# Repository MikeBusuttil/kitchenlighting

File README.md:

# Kitchen lighting

| 12 V minimum wiring                                                          | PCB layout                                                                                |
| ---------------------------------------------------------------------------- | ----------------------------------------------------------------------------------------- |
|  |  |

## Getting started

- install prerequisites
```sh
sudo apt install kicad kicad-symbols kicad-footprints poppler-utils python3-venv
arduino-cli core install arduino:samd
```

- build artifacts
```sh
python3 12v/build.py
python3 5v/build.py
python3 12v/pcb/pcb.py

mkdir -p 12vRGB
cp 12v/min.ino 12vRGB/12vRGB.ino
arduino-cli compile --fqbn arduino:samd:nano_33_iot --output-dir 12vRGB/build 12vRGB
```

- upload sketch to the nano
```sh
arduino-cli board list
nano_port=/dev/ttyACM0  # Replace with your Nano's port from the list above.
arduino-cli upload --fqbn arduino:samd:nano_33_iot  --port "$nano_port" --input-dir 12vRGB/build 12vRGB
```

## Project files

| Design     | Spec                   | Shopping lists                                    | Best practice       | Minimum            |
| ---------- | ---------------------- | ------------------------------------------------- | ------------------- | ------------------ |
| 12 V RGB   | [spec.md](12v/spec.md) | [min.csv](12v/min.csv) · [best.csv](12v/best.csv) | [SVG](12v/best.svg) | [SVG](12v/min.svg) |
| 5 V APA102 | [spec.md](5v/spec.md)  | [min.csv](5v/min.csv) · [best.csv](5v/best.csv)   | [SVG](5v/best.svg)  | [SVG](5v/min.svg)  |

The generated `min.csv` and `best.csv` shopping lists are compatible with DigiKey’s [Upload a List](https://www.digikey.ca/en/mylists/) feature.

## 12 V PCB

| Drawing                                          | PDF                                 |
| ------------------------------------------------ | ----------------------------------- |
| Schematic                                        | [PDF](12v/pcb/pcb.pdf)              |
| Assembly layout, dimensions and component legend | [PDF](12v/pcb/pcb-layout.pdf)       |
| Plated drill map                                 | [PDF](12v/pcb/pcb-PTH-drl_map.pdf)  |
| Non-plated drill map                             | [PDF](12v/pcb/pcb-NPTH-drl_map.pdf) |

| File                                                 | Purpose                             |
| ---------------------------------------------------- | ----------------------------------- |
| [pcb-notes.md](12v/pcb/pcb-notes.md)                 | Design, ordering, wiring and checks |
| [pcb-cost-estimate.md](12v/pcb/pcb-cost-estimate.md) | Prototype budget in CAD             |
| [pcb.kicad_pro](12v/pcb/pcb.kicad_pro)               | Editable KiCad project              |
| [pcb-gerbers.zip](12v/pcb/pcb-gerbers.zip)           | PCB fabrication upload              |
| [pcb-assembly.zip](12v/pcb/pcb-assembly.zip)         | Complete assembly handoff           |
| [pcb-bom.csv](12v/pcb/pcb-bom.csv)                   | Fitted parts                        |
| [pcb-positions.csv](12v/pcb/pcb-positions.csv)       | Placement data                      |
| [pcb-checks.json](12v/pcb/pcb-checks.json)           | Generated verification results      |

```bash
python3 12v/pcb/pcb.py            # check and export the committed CAD
python3 12v/pcb/pcb.py --rebuild  # reconstruct CAD from the circuit and saved routing
python3 -m unittest discover -s 12v/pcb -p 'test_*.py'
python3 12v/pcb/browser_exports.py  # refresh browser versions of all repository PDFs
```

## Tests

```sh
python3 -m unittest discover -s .utils -p 'test_*.py'
g++ -std=c++11 -Wall -Wextra -Werror -I12v/tests 12v/tests/test_min.cpp -o /tmp/kitchenlighting-test-min
/tmp/kitchenlighting-test-min
```

## Contributing

- markdown tables: `|`s should line up
- diagram preferences:
  - show part numbers; avoid reference codes
  - maximize readability:
    - shorter wires is better
  - avoid using a legend:
    - label components directly
    - draw all connections
  - avoid redundancy (ie. explaining a connection that the diagram clearly displays)

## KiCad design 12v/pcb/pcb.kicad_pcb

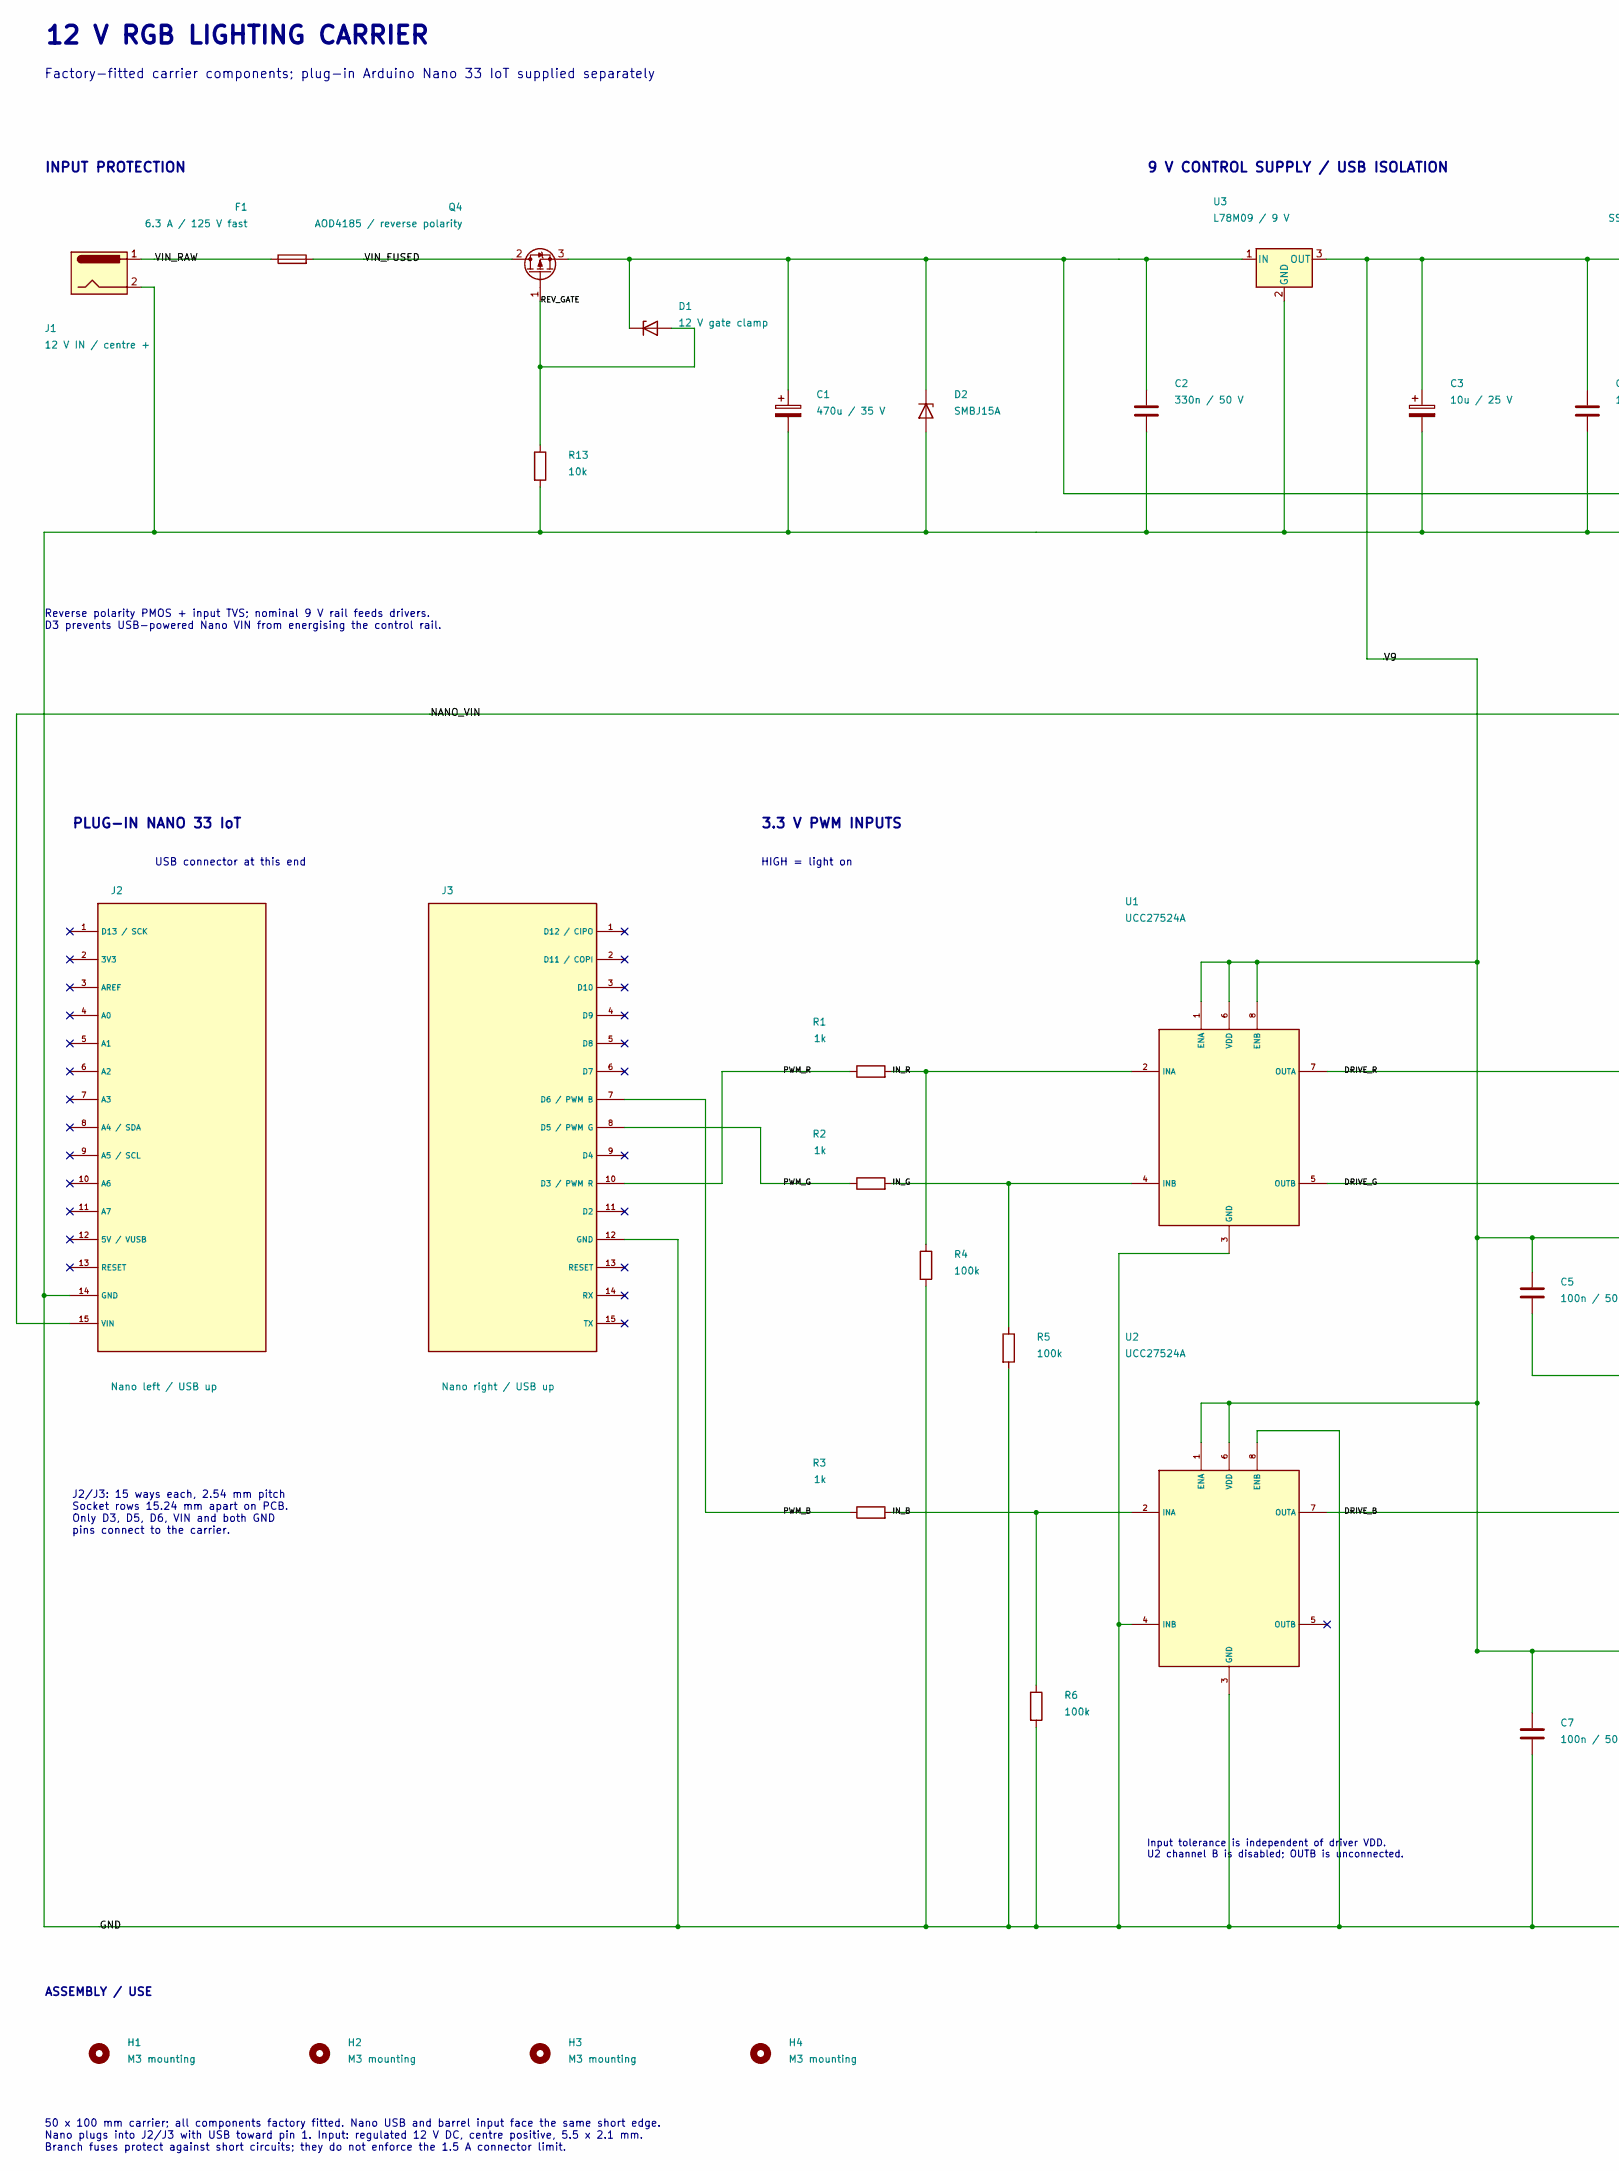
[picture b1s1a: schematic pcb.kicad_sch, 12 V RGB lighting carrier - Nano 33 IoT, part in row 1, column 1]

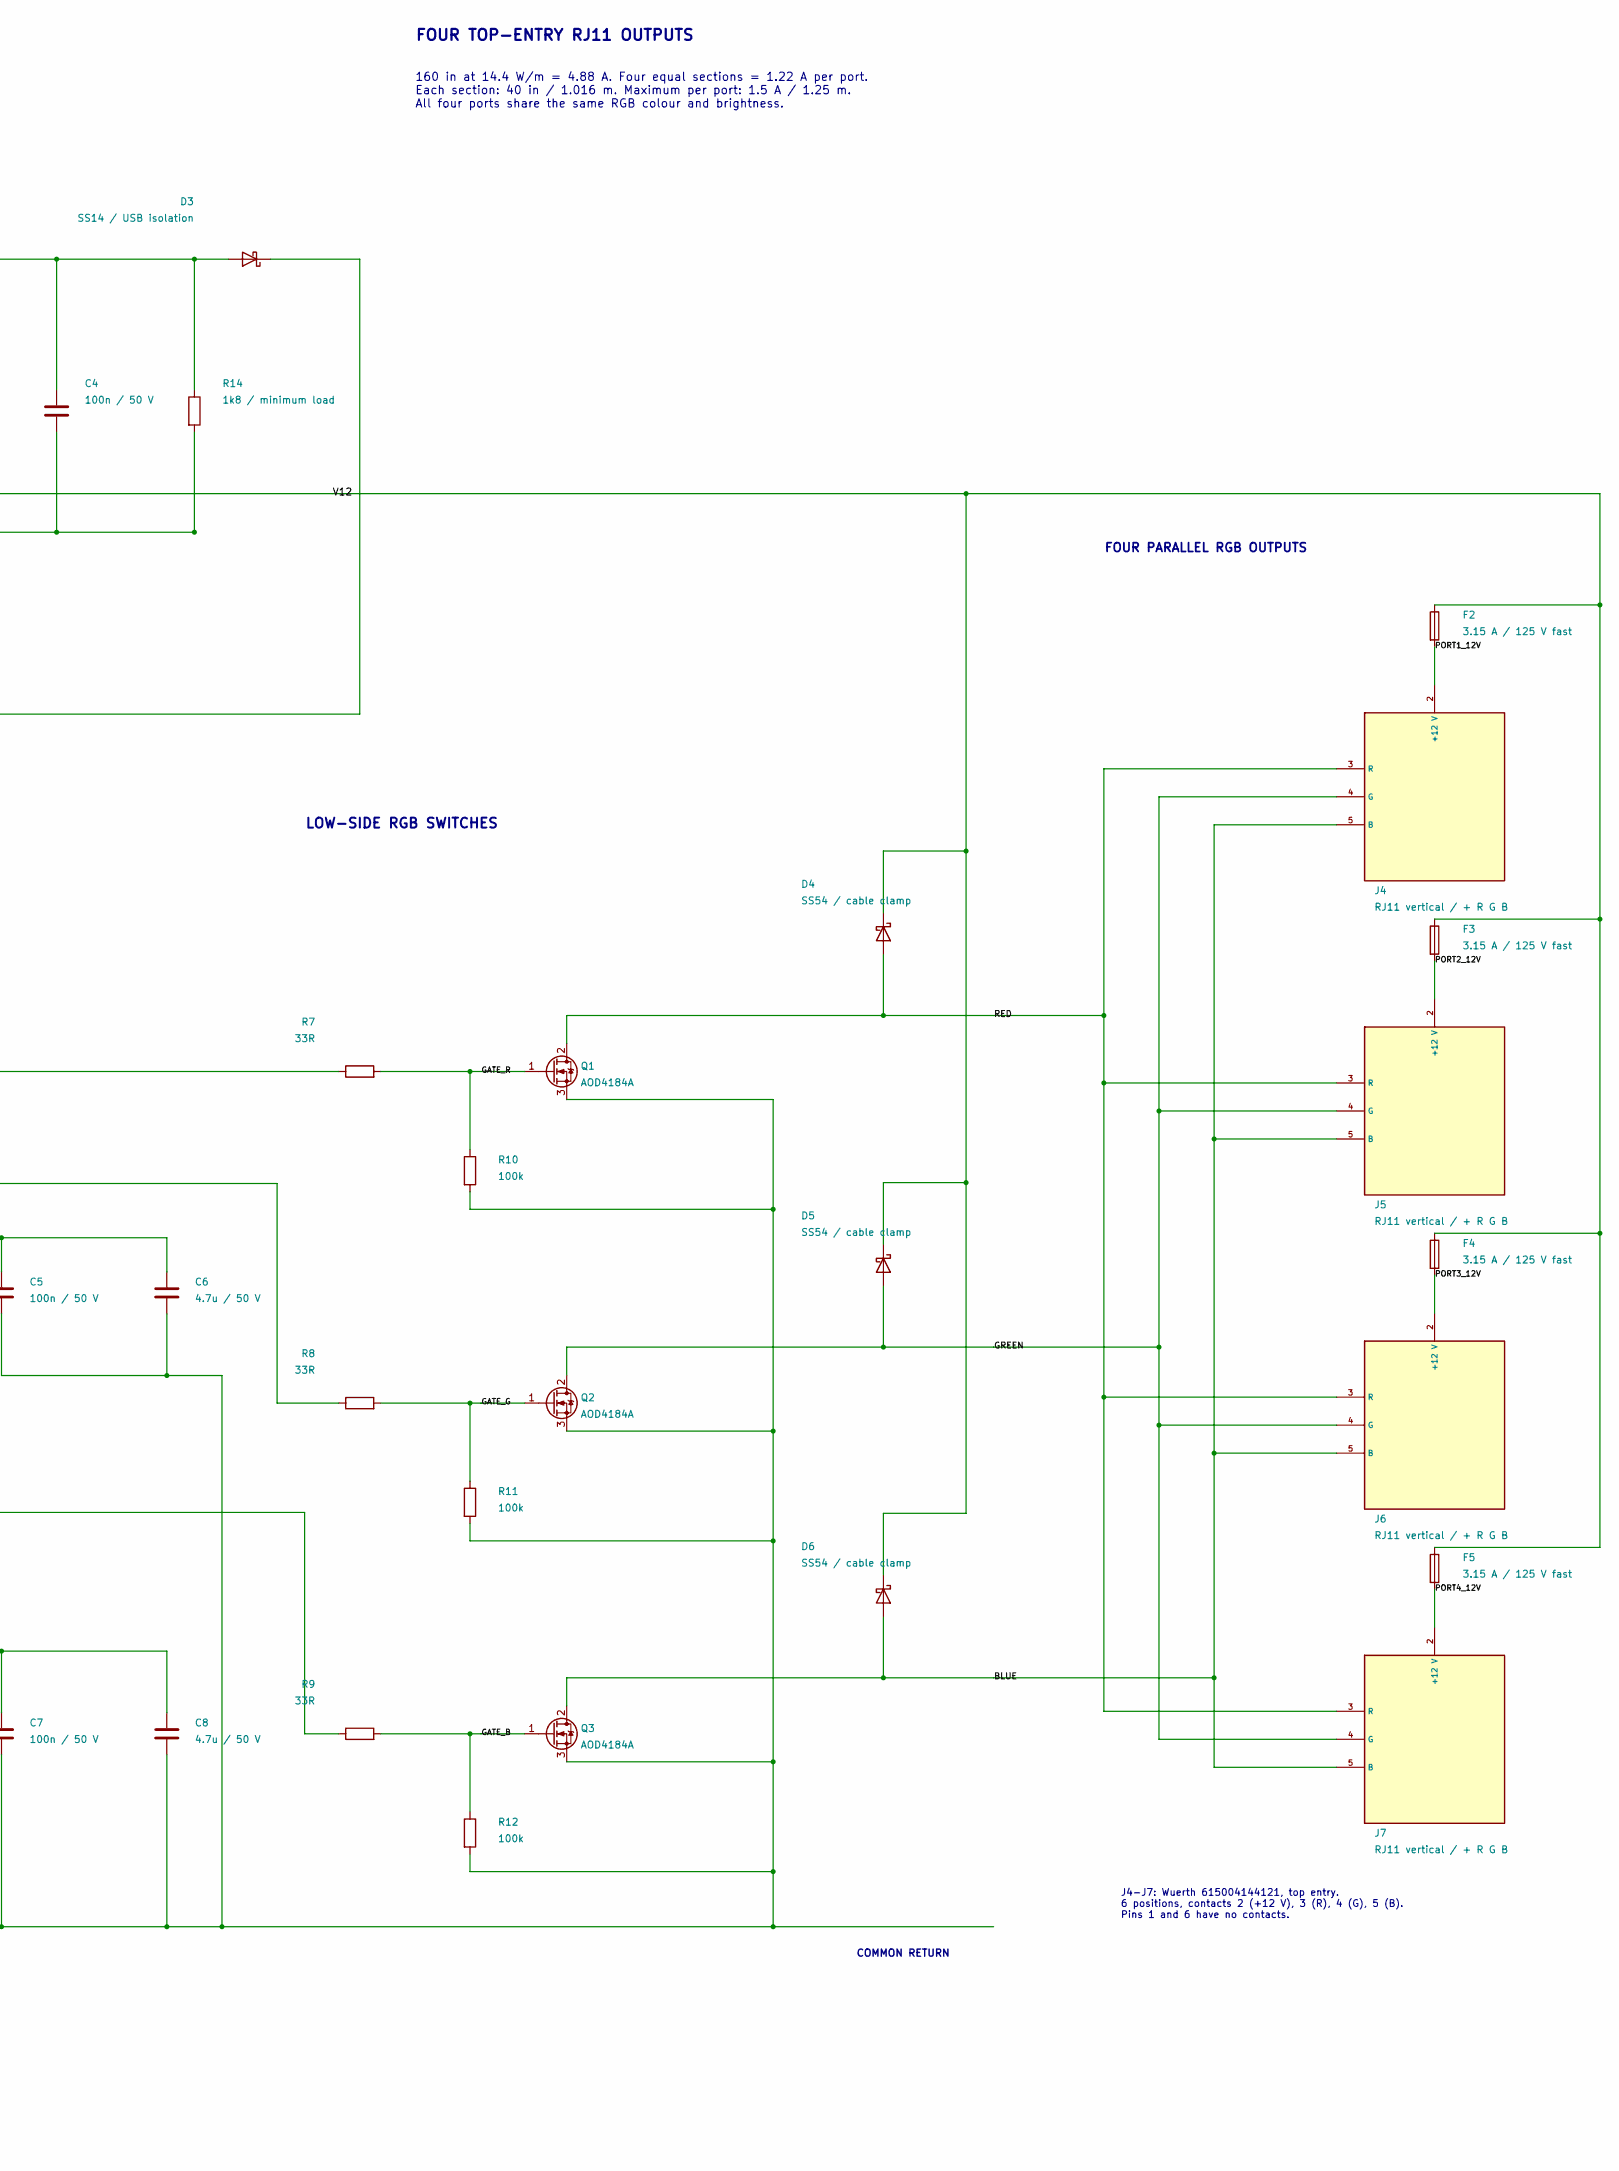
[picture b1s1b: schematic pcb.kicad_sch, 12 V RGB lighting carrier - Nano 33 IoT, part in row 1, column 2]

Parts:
C1: 470u / 35 V; CP_Elec_10x10.5; MPN EEHZL1V471P
C2: 330n / 50 V; C_0805_2012Metric; MPN GRM21BR71H334KA01L
C3: 10u / 25 V; CP_Elec_4x5.8; MPN EEEFK1E100R
C4, C5, C7: 100n / 50 V; C_0805_2012Metric; MPN GRM21BR71H104KA01L
C6, C8: 4.7u / 50 V; C_1210_3225Metric; MPN GRM32ER71H475KA88L
D1: 12 V gate clamp; D_SOD-123; MPN BZT52C12-7-F
D2: SMBJ15A; D_SMB; MPN SMBJ15A
D3: SS14 / USB isolation; D_SMA; MPN SS14-E3/61T
D4, D5, D6: SS54 / cable clamp; D_SMC; MPN SSC54-E3/57T
F1: 6.3 A / 125 V fast; Fuse_Littelfuse-NANO2-451_453; MPN 045106.3MRL
F2, F3, F4, F5: 3.15 A / 125 V fast; Fuse_Littelfuse-NANO2-451_453; MPN 04513.15MRL
H1, H2, H3, H4: M3 mounting; MountingHole_3.2mm_M3
J1: 12 V IN / centre +; BarrelJack_CUI_PJ-063AH_Horizontal; MPN PJ-063AH
J2: Nano left / USB up; Socket_Samtec_SSQ-115-01-G-S; MPN SSQ-115-01-G-S
J3: Nano right / USB up; Socket_Samtec_SSQ-115-01-G-S; MPN SSQ-115-01-G-S
J4, J5, J6, J7: RJ11 vertical / + R G B; RJ11_Wuerth_615004144121; MPN 615004144121
Q1, Q2, Q3: AOD4184A; TO-252-3_TabPin2; MPN AOD4184A
Q4: AOD4185 / reverse polarity; TO-252-3_TabPin2; MPN AOD4185
R1, R2, R3: 1k; R_0805_2012Metric; MPN RC0805FR-071KL
R4, R5, R6, R10, R11, R12: 100k; R_0805_2012Metric; MPN RC0805FR-07100KL
R7, R8, R9: 33R; R_0805_2012Metric; MPN RC0805FR-0733RL
R13: 10k; R_0805_2012Metric; MPN RC0805FR-0710KL
R14: 1k8 / minimum load; R_0805_2012Metric; MPN RC0805FR-071K8L
U1, U2: UCC27524A; SOIC-8_3.9x4.9mm_P1.27mm; MPN UCC27524ADR
U3: L78M09 / 9 V; TO-252-3_TabPin2; MPN L78M09CDT-TR

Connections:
BLUE: D6.2 (A), J4.5 (B), J5.5 (B), J6.5 (B), J7.5 (B), Q3.2 (D)
DRIVE_B: R9.1, U2.7 (OUTA)
DRIVE_G: R8.1, U1.5 (OUTB)
DRIVE_R: R7.1, U1.7 (OUTA)
GATE_B: Q3.1 (G), R9.2, R12.1
GATE_G: Q2.1 (G), R8.2, R11.1
GATE_R: Q1.1 (G), R7.2, R10.1
GND: C1.2, C2.2, C3.2, C4.2, C5.2, C6.2, C7.2, C8.2, D2.2 (A), J1.2, J2.14 (GND), J3.12 (GND), Q1.3 (S), Q2.3 (S), Q3.3 (S), R4.2, R5.2, R6.2, R10.2, R11.2, R12.2, R13.2, R14.2, U1.3 (GND), U2.3 (GND), U2.4 (INB), U2.8 (ENB), U3.2 (GND)
GREEN: D5.2 (A), J4.4 (G), J5.4 (G), J6.4 (G), J7.4 (G), Q2.2 (D)
IN_B: R3.2, R6.1, U2.2 (INA)
IN_G: R2.2, R5.1, U1.4 (INB)
IN_R: R1.2, R4.1, U1.2 (INA)
NANO_VIN: D3.1 (K), J2.15 (VIN)
PORT1_12V: F2.2, J4.2 (+12 V)
PORT2_12V: F3.2, J5.2 (+12 V)
PORT3_12V: F4.2, J6.2 (+12 V)
PORT4_12V: F5.2, J7.2 (+12 V)
PWM_B: J3.7 (D6 / PWM B), R3.1
PWM_G: J3.8 (D5 / PWM G), R2.1
PWM_R: J3.10 (D3 / PWM R), R1.1
RED: D4.2 (A), J4.3 (R), J5.3 (R), J6.3 (R), J7.3 (R), Q1.2 (D)
REV_GATE: D1.2 (A), Q4.1 (G), R13.1
V9: C3.1, C4.1, C5.1, C6.1, C7.1, C8.1, D3.2 (A), R14.1, U1.1 (ENA), U1.6 (VDD), U1.8 (ENB), U2.1 (ENA), U2.6 (VDD), U3.3 (OUT)
V12: C1.1, C2.1, D1.1 (K), D2.1 (K), D4.1 (K), D5.1 (K), D6.1 (K), F2.1, F3.1, F4.1, F5.1, Q4.3 (S), U3.1 (IN)
VIN_FUSED: F1.2, Q4.2 (D)
VIN_RAW: F1.1, J1.1

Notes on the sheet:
12 V RGB LIGHTING CARRIER
Factory-fitted carrier components; plug-in Arduino Nano 33 IoT supplied separately
FOUR TOP-ENTRY RJ11 OUTPUTS
160 in at 14.4 W/m = 4.88 A. Four equal sections = 1.22 A per port. Each section: 40 in / 1.016 m. Maximum per port: 1.5 A / 1.25 m. All four ports share the same RGB colour and brightness.
COMMON RETURN
INPUT PROTECTION
9 V CONTROL SUPPLY / USB ISOLATION
Reverse polarity PMOS + input TVS; nominal 9 V rail feeds drivers. D3 prevents USB-powered Nano VIN from energising the control rail.
PLUG-IN NANO 33 IoT
USB connector at this end
J2/J3: 15 ways each, 2.54 mm pitch Socket rows 15.24 mm apart on PCB. Only D3, D5, D6, VIN and both GND pins connect to the carrier.
3.3 V PWM INPUTS
HIGH = light on
Input tolerance is independent of driver VDD. U2 channel B is disabled; OUTB is unconnected.
LOW-SIDE RGB SWITCHES
FOUR PARALLEL RGB OUTPUTS
J4-J7: Wuerth 615004144121, top entry. 6 positions, contacts 2 (+12 V), 3 (R), 4 (G), 5 (B). Pins 1 and 6 have no contacts.
ASSEMBLY / USE
50 x 100 mm carrier; all components factory fitted. Nano USB and barrel input face the same short edge. Nano plugs into J2/J3 with USB toward pin 1. Input: regulated 12 V DC, centre positive, 5.5 x 2.1 mm. Branch fuses protect against short circuits; they do not enforce the 1.5 A connector limit.

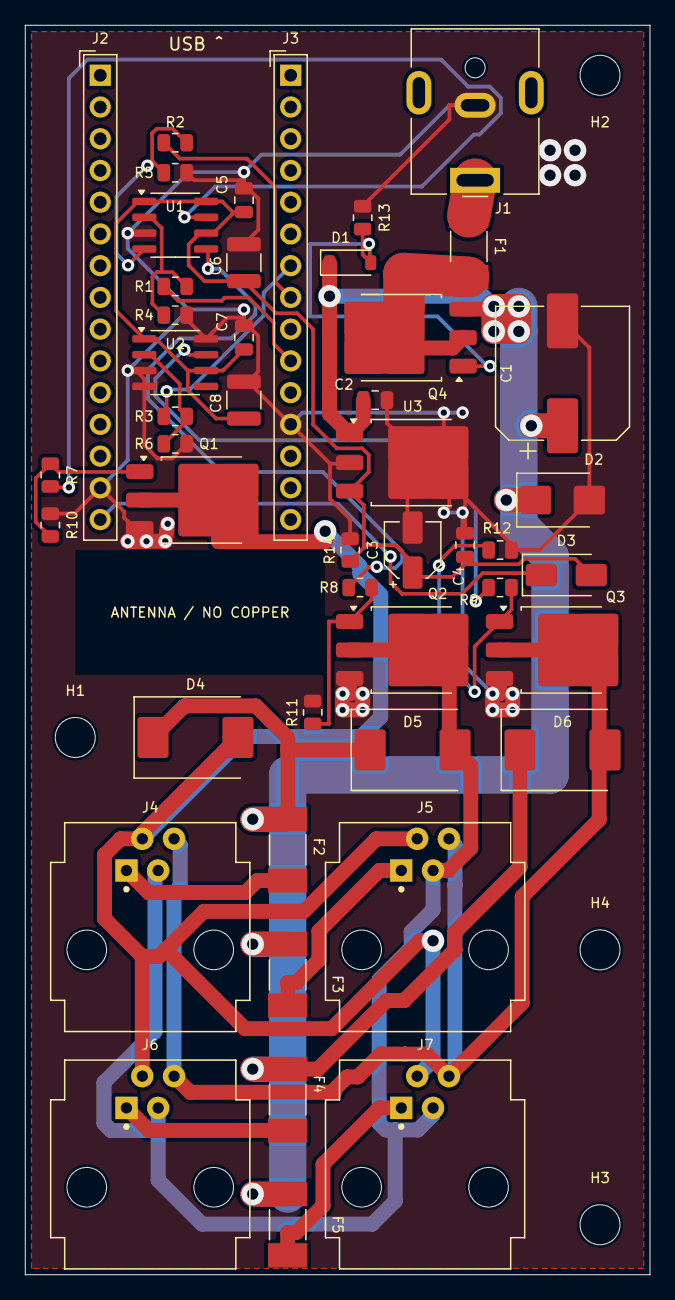
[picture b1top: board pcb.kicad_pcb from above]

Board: 2 copper layers, 50.0 x 100.0 mm, 51 parts (0 on the bottom side), 26 nets.

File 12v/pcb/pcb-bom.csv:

Designator,Quantity,Value,Manufacturer Part Number,Footprint,Assembly,Notes
J1,1,12 V IN / centre +,PJ-063AH,Connector_BarrelJack:BarrelJack_CUI_PJ-063AH_Horizontal,THT factory solder,8 A jack; 5.5 x 2.1 mm mating plug; plated slots required
J2,1,Nano left / USB up,SSQ-115-01-G-S,pcb:Socket_Samtec_SSQ-115-01-G-S,THT factory solder,2.54 mm pitch; two rows 15.24 mm apart; socket body height 8.51 mm
J3,1,Nano right / USB up,SSQ-115-01-G-S,pcb:Socket_Samtec_SSQ-115-01-G-S,THT factory solder,2.54 mm pitch; two rows 15.24 mm apart; socket body height 8.51 mm
"J4,J5,J6,J7",4,RJ11 vertical / + R G B,615004144121,pcb:RJ11_Wuerth_615004144121,THT factory solder,"Top-entry 6P4C; 1.5 A/contact; 1.25 m maximum strip at 14.4 W/m, 12 V"
F1,1,6.3 A / 125 V fast,045106.3MRL,Fuse:Fuse_Littelfuse-NANO2-451_453,Top SMT,
Q4,1,AOD4185 / reverse polarity,AOD4185,Package_TO_SOT_SMD:TO-252-3_TabPin2,Top SMT,
R13,1,10k,RC0805FR-0710KL,Resistor_SMD:R_0805_2012Metric,Top SMT,
D1,1,12 V gate clamp,BZT52C12-7-F,Diode_SMD:D_SOD-123,Top SMT,
D2,1,SMBJ15A,SMBJ15A,Diode_SMD:D_SMB,Top SMT,
C1,1,470u / 35 V,EEHZL1V471P,Capacitor_SMD:CP_Elec_10x10.5,Top SMT,
"F2,F3,F4,F5",4,3.15 A / 125 V fast,04513.15MRL,Fuse:Fuse_Littelfuse-NANO2-451_453,Top SMT,Short-circuit fuse; does NOT protect the 1.5 A RJ11 contact from overload
U3,1,L78M09 / 9 V,L78M09CDT-TR,Package_TO_SOT_SMD:TO-252-3_TabPin2,Top SMT,
C2,1,330n / 50 V,GRM21BR71H334KA01L,Capacitor_SMD:C_0805_2012Metric,Top SMT,
C3,1,10u / 25 V,EEEFK1E100R,Capacitor_SMD:CP_Elec_4x5.8,Top SMT,
"C4,C5,C7",3,100n / 50 V,GRM21BR71H104KA01L,Capacitor_SMD:C_0805_2012Metric,Top SMT,
R14,1,1k8 / minimum load,RC0805FR-071K8L,Resistor_SMD:R_0805_2012Metric,Top SMT,
D3,1,SS14 / USB isolation,SS14-E3/61T,Diode_SMD:D_SMA,Top SMT,
"U1,U2",2,UCC27524A,UCC27524ADR,Package_SO:SOIC-8_3.9x4.9mm_P1.27mm,Top SMT,"Dual noninverting driver; input voltage independent of supply; used enables high, unused channel grounded"
"C6,C8",2,4.7u / 50 V,GRM32ER71H475KA88L,Capacitor_SMD:C_1210_3225Metric,Top SMT,
"Q1,Q2,Q3",3,AOD4184A,AOD4184A,Package_TO_SOT_SMD:TO-252-3_TabPin2,Top SMT,
"R1,R2,R3",3,1k,RC0805FR-071KL,Resistor_SMD:R_0805_2012Metric,Top SMT,
"R4,R10,R5,R11,R6,R12",6,100k,RC0805FR-07100KL,Resistor_SMD:R_0805_2012Metric,Top SMT,
"R7,R8,R9",3,33R,RC0805FR-0733RL,Resistor_SMD:R_0805_2012Metric,Top SMT,
"D4,D5,D6",3,SS54 / cable clamp,SSC54-E3/57T,Diode_SMD:D_SMC,Top SMT,

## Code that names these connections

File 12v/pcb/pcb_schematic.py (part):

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    add('D2', 180, 90, 270, symbol='Device:D_Zener', reference_at=(185, 87), value_at=(185, 90))
    s.wire(pin('J1', 1), pin('F1', 1))
    s.wire(pin('F1', 2), pin('Q4', 2))
    s.label('VIN_RAW', 40, 62.46)
    s.label('VIN_FUSED', 78, 62.46)
    s.wire(pin('Q4', 3), (215, 62.46))
    link('D1', 1, (126.19, 62.46)); join(126.19, 62.46)
    link('D1', 2, (138, 75), (138, 82), (110, 82), pin('Q4', 1))
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    join(260, 62.46)
    s.label('V9', 263, 135)
    link('D3', 1, (355, 62.46), (355, 145), (15, 145), (15, 255.56))
    s.label('NANO_VIN', 90, 145)
    s.text('Reverse polarity PMOS + input TVS; nominal 9 V rail feeds drivers.\nD3 prevents USB-powered Nano VIN from energising the control rail.', 20, 128, size=1.35)

    s.text('PLUG-IN NANO 33 IoT', 25, 165, size=1.8, bold=True)
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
